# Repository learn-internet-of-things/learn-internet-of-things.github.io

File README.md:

README
======

Jekyll
------

### Windows

Ruby 2.2.5 (x64)

http://rubyinstaller.org/downloads/

Install it for example to `C:\Tools\Ruby22-x64`
Select checkbox "Add Ruby executables to your PATH"

DevKit "for use with Ruby 2.0 and above (x64 - 64bits only)"

http://rubyinstaller.org/downloads/

`C:\Tools\DevKit2`
Add `C:\Tools\DevKit2\bin` to PATH

CMD to `C:\Tools\DevKit2`

```
ruby dk.rb init
ruby dk.rb install
```

Open CMD window.

```
gem install RedCloth -v '4.2.9
gem install bundler
```

Change in CMD to Github pages reposity

```
bundle install
```

Then, the `server.bat` can be used to start the server.

Notes
-----

Markdown

http://kramdown.gettalong.org/quickref.html#footnotes

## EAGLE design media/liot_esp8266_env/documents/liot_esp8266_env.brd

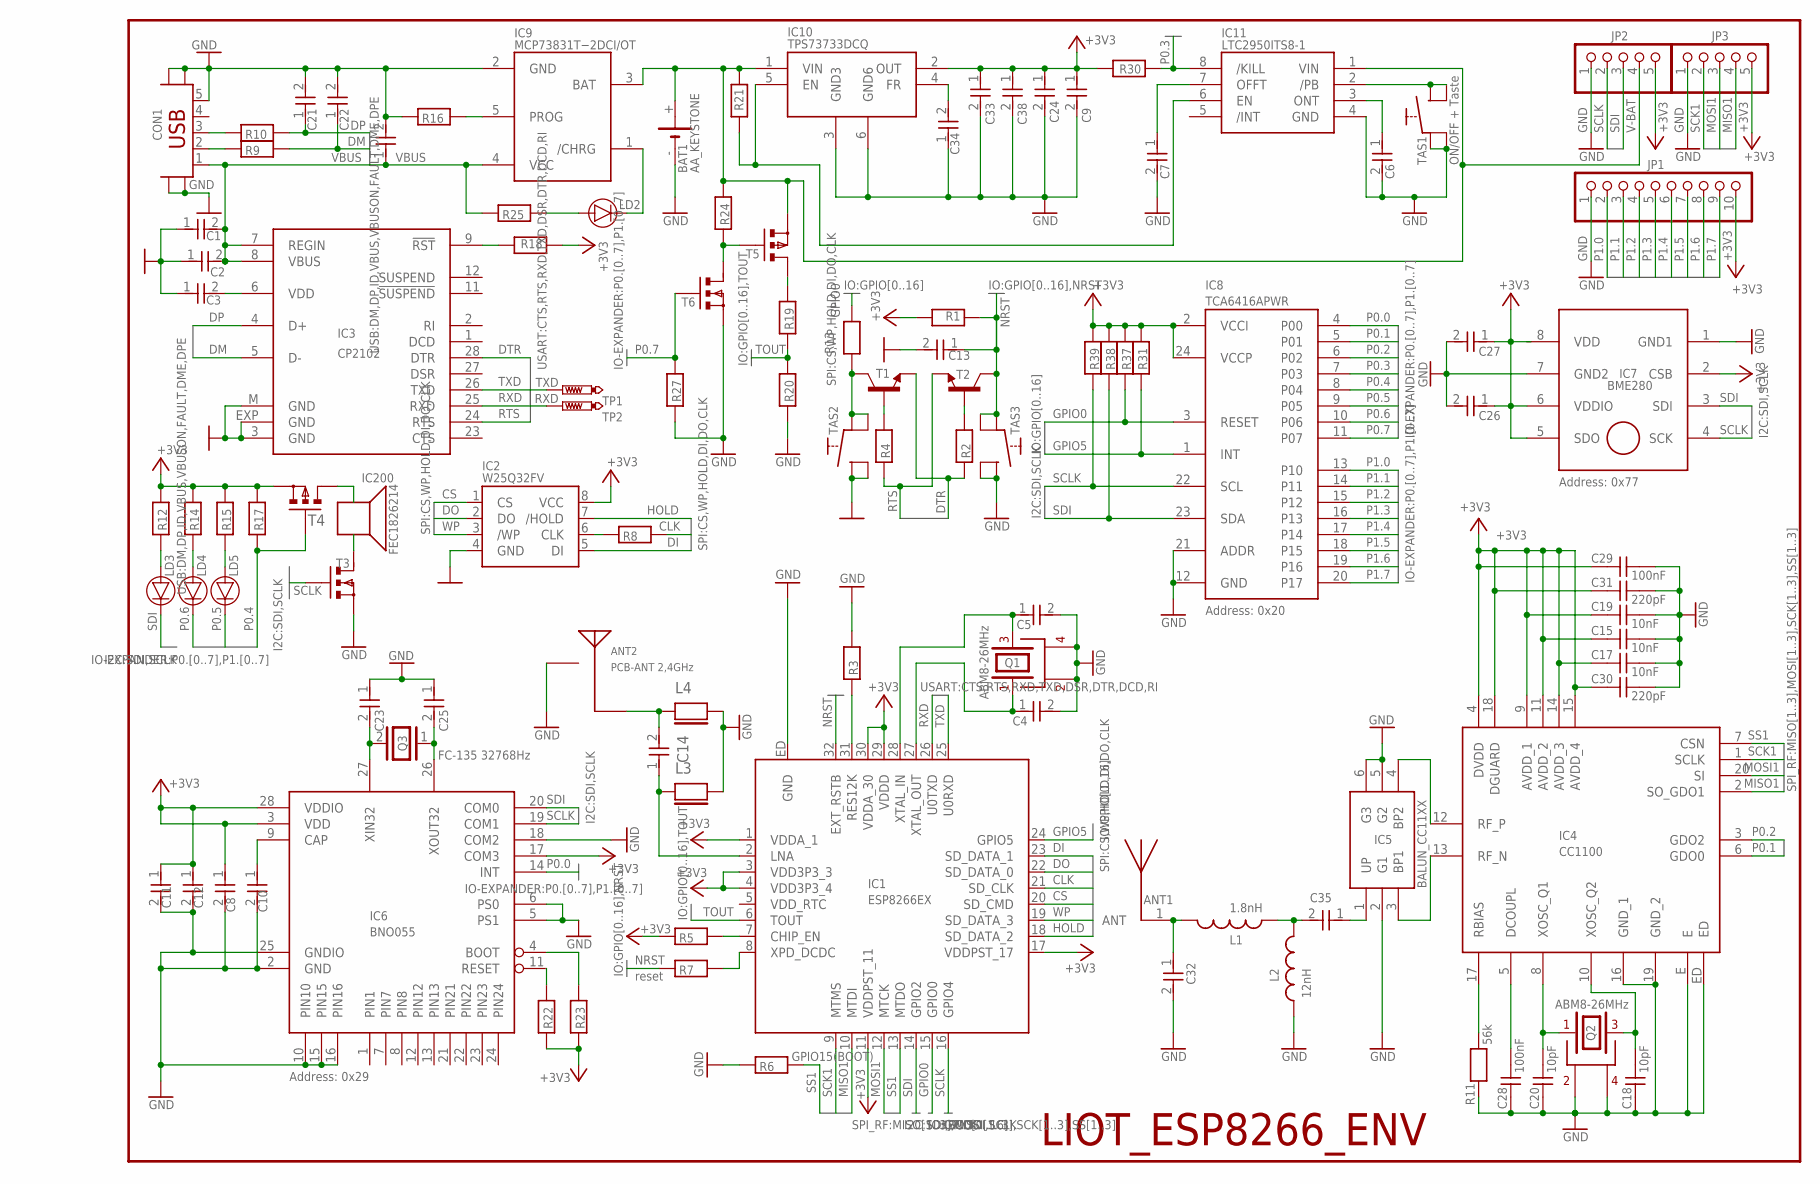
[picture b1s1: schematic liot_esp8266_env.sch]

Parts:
ANT1: ANT_868MHZ
ANT2: PCB-ANT 2,4GHz; 2.4GHZ_PCB
BAT1: AA_KEYSTONE
C1, C2, C3: 1U-16VX7R_0805; C0805
C4, C5, C32: 10P-50VCOG_0603; C0603
C6, C8, C10, C12, C24, C26, C27: 100N-50VX7R_0603; C0603
C7: 330N-16VX7R_0603; C0603
C9: XX-XX-X7R_1210; C1210
C11: 6N8-50VX7R_0603; C0603
C13: 470P-50VX7R_0603; C0603
C14: 5.6pF; C0402
C15, C17, C19: 10nF; C0603
C16, C34: XX-XX-X7R_0805; C0805
C18, C20: 10pF; C0603
C21, C22: 47P-50VCOG_0603; C0603
C23, C25: 22P-50VNP0_0603; C0603
C28, C29: 100nF; C0603
C30, C31: 220pF; C0603
C33, C38: XX-XX-NB-X7R_1210; C1210
C35: 100P-50VCOG_0603; C0603
CON1: MICRO-USB-A/B; MICRO_USB_A/B
IC1: ESP8266EX
IC2: W25Q32FV; SOIC-8_208MIL
IC3: CP2102; MLP28
IC4: CC1100; QLP20E-1+
IC5: BALUN_CC11XX
IC6: BNO055
IC7: BME280
IC8: TCA6416APWR; TSSOP24
IC9: MCP73831T−2DCI/OT; TSOT-23
IC10: TPS73733DCQ; SOT223-6
IC11: LTC2950ITS8-1; TS8
IC200: FEC1826214; BEEPER5X5
JP1: PINHD-1X10; 1X10
JP2, JP3: PINHD-1X5; 1X05
L1: 1.8nH; 0603
L2: 12nH; 0603
L3, L4: NC; L0402
LD2, LD3, LD4, LD5: XXX_0603_H04; LD0603_H04
MA_BS1, MA_BS2: MA_BS_L; MARK_L
MA_LS1, MA_LS2: MA_LS_L; MARK_L
Q1, Q2: ABM8-26MHz; ABM8G
Q3: FC-135 32768Hz; FC-135
R1, R2, R3, R4, R5, R6: 12K-1%_0603; R0603
R7: 0R-1%_0603; R0603
R8: 200R-1%_0603; R0603
R9, R10: 22R-1%_0603; R0603
R11: 56k; R0603
R12, R14, R15, R17: 1K-1%_0603; R0603
R13: 220R-1%_0603; R0603
R16: 2K-1%_0603; R0603
R18, R22, R23, R24, R27, R31, R37, R38, R39: 10K-1%_0603; R0603
R19: 390K-1%_0603; R0603
R20, R21, R30: 100K-1%_0603; R0603
R25: 680R-1%_0603; R0603
T1, T2: BC817-NPN-SOT23-BEC; SOT23-BEC
T3, T6: IRLML2402; SOT23S23
T4, T5: IRLML6402; SOT23S23
TAS1, TAS2, TAS3: 434333045822; TAWU1_S_H18
TP1, TP2: PTR1B1,27; B1,27

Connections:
+3V3: C8.1, C9.1, C11.1, C12.1, C15.1, C17.1, C19.1, C24.1, C26.1, C27.1, C29.1, C30.1, C31.1, C33.1, C38.1, IC1.1 (VDDA_1), IC1.3 (VDD3P3_3), IC1.4 (VDD3P3_4), IC1.11 (VDDPST_11), IC1.17 (VDDPST_17), IC1.29 (VDDD), IC1.30 (VDDA_30), IC2.8 (VCC), IC4.4 (DVDD), IC4.9 (AVDD_1), IC4.11 (AVDD_2), IC4.14 (AVDD_3), IC4.15 (AVDD_4), IC4.18 (DGUARD), IC6.3 (VDD), IC6.17 (COM3), IC6.28 (VDDIO), IC7.2 (CSB), IC7.5 (SDO), IC7.6 (VDDIO), IC7.8 (VDD), IC8.2 (VCCI), IC8.24 (VCCP), IC10.2 (OUT), JP1.10, JP2.5, JP3.5, R1.2, R5.1, R12.2, R14.2, R15.2, R17.2, R18.1, R22.1, R23.1, R30.2, R31.2, R37.2, R38.2, R39.2, T4.2 (S)
/PB: IC11.2 (/PB), TAS1.2 (ON), TAS1.4 (ON1)
CLK: IC1.21 (SD_CLK), R8.2
CS: IC1.20 (SD_CMD), IC2.1 (CS)
DI: IC1.23 (SD_DATA_1), IC2.5 (DI)
DM: C22.1, IC3.5 (D-), R9.1
DME: CON1.2 (D-), R9.2
DO: IC1.22 (SD_DATA_0), IC2.2 (DO)
DP: C21.1, IC3.4 (D+), R10.1
DPE: CON1.3 (D+), R10.2
DTR: IC3.28 (DTR), R2.1, T1.E
GND: ANT2.GND (2), BAT1.-, C1.1, C2.1, C3.1, C4.2, C5.2, C6.2, C7.2, C8.2, C9.2, C10.2, C11.2, C12.2, C13.2, C15.2, C16.2, C17.2, C18.1, C19.2, C20.1, C21.2, C22.2, C23.1, C24.2, C25.1, C26.2, C27.2, C28.1, C29.2, C30.2, C31.2, C32.2, C33.2, C34.1, C38.2, CON1.5 (GND), CON1.S1 (GND), CON1.S2 (GND), CON1.S3 (GND), CON1.S4 (GND), CON1.S5 (GND), CON1.S6 (GND), CON1.S7 (GND), CON1.S8 (GND), CON1.S9 (GND), CON1.S10 (GND), CON1.S11 (GND), CON1.S12 (GND), IC1.ED (GND), IC2.4 (GND), IC3.3 (GND), IC3.EXP (GND), IC3.M (GND), IC4.16 (GND_1), IC4.19 (GND_2), IC4.E, IC4.ED, IC5.2 (G1), IC5.5 (G2), IC5.6 (G3), IC6.2 (GND), IC6.5 (PS1), IC6.6 (PS0), IC6.10 (PIN10), IC6.15 (PIN15), IC6.16 (PIN16), IC6.18 (COM2), IC6.25 (GNDIO), IC7.1 (GND1), IC7.7 (GND2), IC8.12 (GND), IC8.21 (ADDR), IC9.2 (GND), IC10.3 (GND3), IC10.6 (GND6), IC11.4 (GND), JP1.1, JP2.1, JP3.1, L2.1, L3.2, L4.2, Q1.2, Q1.4, Q2.2, Q2.4, R3.2, R6.1, R11.1, R16.1, R20.2, R27.1, T3.2 (S), T6.2 (S), TAS1.1 (COMM), TAS1.3 (COMM1), TAS2.2 (ON), TAS2.4 (ON1), TAS3.2 (ON), TAS3.4 (ON1)
GPIO0: IC1.15 (GPIO0), IC8.3 (RESET), R13.2, R37.1
GPIO5: IC1.24 (GPIO5), IC8.1 (INT), R31.1
HOLD: IC1.18 (SD_DATA_2), IC2.7 (/HOLD)
IC12: IC200.-, T3.3 (D)
MISO1: IC1.10 (MTDI), IC4.2 (SO_GDO1), JP3.4
MOSI1: IC1.12 (MTCK), IC4.20 (SI), JP3.3
unnamed: C4.1, IC1.27 (XTAL_OUT), Q1.1
unnamed: R2.2, T2.B
unnamed: C3.2, IC3.6 (VDD)
unnamed: IC1.7 (CHIP_EN), R5.2
unnamed: R4.2, T1.B
unnamed: IC1.31 (RES12K), R3.1
unnamed: IC1.8 (XPD_DCDC), R7.1
unnamed: IC2.6 (CLK), R8.1
unnamed: C14.1, IC1.2 (LNA), L3.1
unnamed: C18.2, IC4.10 (XOSC_Q2), Q2.3
unnamed: C20.2, IC4.8 (XOSC_Q1), Q2.1
unnamed: IC4.17 (RBIAS), R11.2
unnamed: C28.2, IC4.5 (DCOUPL)
unnamed: C5.1, IC1.28 (XTAL_IN), Q1.3
unnamed: IC9.5 (PROG), R16.2
unnamed: IC9.1 (/CHRG), LD2.2 (K)
unnamed: IC4.13 (RF_N), IC5.3 (BP1)
unnamed: IC4.12 (RF_P), IC5.4 (BP2)
unnamed: ANT1.1, C32.1, L1.2
unnamed: LD2.1 (A), R25.1
unnamed: C35.2, L1.1, L2.2
unnamed: C35.1, IC5.1 (UP)
unnamed: ANT2.ANT (1), C14.2, L4.1
unnamed: IC6.11 (RESET), R22.2
unnamed: IC6.4 (BOOT), R23.2
unnamed: C10.1, IC6.9 (CAP)
unnamed: C23.2, IC6.27 (XIN32), Q3.2
unnamed: IC10.5 (EN), IC11.6 (EN), R21.1
unnamed: C25.2, IC6.26 (XOUT32), Q3.1
unnamed: R13.1, T1.C, TAS2.1 (COMM), TAS2.3 (COMM1)
unnamed: C34.2, IC10.4 (FR)
unnamed: IC200.+, T4.3 (D)
unnamed: LD3.1 (A), R12.1
unnamed: LD4.1 (A), R14.1
unnamed: IC3.9 (!RST), R18.2
unnamed: LD5.1 (A), R15.1
unnamed: R19.2, T5.3 (D)
unnamed: R24.1, T5.1 (G), T6.3 (D)
unnamed: C7.1, IC11.7 (OFFT)
unnamed: C6.1, IC11.3 (ONT)
NRST: C13.1, IC1.32 (EXT_RSTB), R1.1, R7.2, T2.C, TAS3.1 (COMM), TAS3.3 (COMM1)
P0.0: IC6.14 (INT), IC8.4 (P00)
P0.1: IC4.6 (GDO0), IC8.5 (P01)
P0.2: IC4.3 (GDO2), IC8.6 (P02)
P0.3: IC8.7 (P03), IC11.8 (/KILL), R30.1
P0.4: IC8.8 (P04), R17.1, T4.1 (G)
P0.5: IC8.9 (P05), LD5.2 (K)
P0.6: IC8.10 (P06), LD4.2 (K)
P0.7: IC8.11 (P07), R27.2, T6.1 (G)
P1.0: IC8.13 (P10), JP1.2
P1.1: IC8.14 (P11), JP1.3
P1.2: IC8.15 (P12), JP1.4
P1.3: IC8.16 (P13), JP1.5
P1.4: IC8.17 (P14), JP1.6
P1.5: IC8.18 (P15), JP1.7
P1.6: IC8.19 (P16), JP1.8
P1.7: IC8.20 (P17), JP1.9
RTS: IC3.24 (RTS), R4.1, T2.E
RXD: IC1.26 (U0TXD), IC3.25 (RXD), TP2.PP
SCK1: IC1.9 (MTMS), IC4.1 (SCLK), JP3.2
SCLK: IC1.16 (GPIO4), IC6.19 (COM1), IC7.4 (SCK), IC8.22 (SCL), JP2.2, R39.1, T3.1 (G)
SDI: IC1.14 (GPIO2), IC6.20 (COM0), IC7.3 (SDI), IC8.23 (SDA), JP2.3, LD3.2 (K), R38.1
SS1: IC1.13 (MTDO), IC4.7 (CSN), R6.2
TOUT: IC1.6 (TOUT), R19.1, R20.1
TXD: IC1.25 (U0RXD), IC3.26 (TXD), TP1.PP
V-BAT: BAT1.+, IC9.3 (BAT), IC10.1 (VIN), IC11.1 (VIN), JP2.4, R21.2, R24.2, T5.2 (S)
VBUS: C1.2, C2.2, C16.1, CON1.1 (VBUS), IC3.7 (REGIN), IC3.8 (VBUS), IC9.4 (VCC), R25.2
WP: IC1.19 (SD_DATA_3), IC2.3 (/WP)

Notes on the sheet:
ON/OFF + Taste
reset
Address: 0x77
Address: 0x29
Address: 0x20
GPIO15(BOOT)
LIOT_ESP8266_ENV

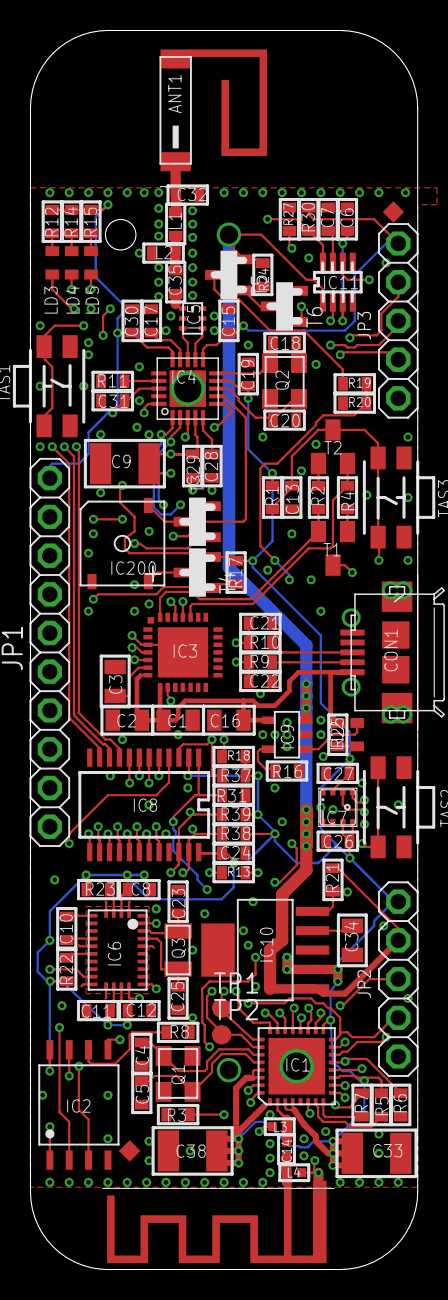
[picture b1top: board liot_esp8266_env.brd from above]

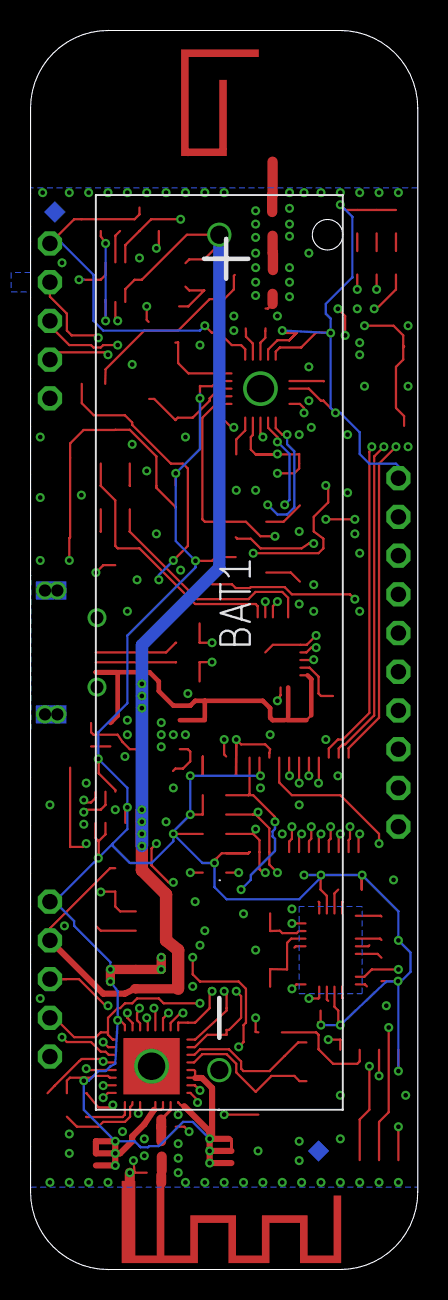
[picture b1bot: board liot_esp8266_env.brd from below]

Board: 4 copper layers, 25.4 x 81.3 mm, 112 parts (3 on the bottom side), 86 nets.

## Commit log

2016-05-26 Sidebar-Nav is working for subpaths now, but not for root
2016-05-26 Add all other jekyll files
2016-05-26 Sidebar-Nav seems to work now also for the root path
2016-05-26 Show only paes in Sidebar-Nav that have a title
2016-05-26 Remove unused order number from page directories.
2016-05-26 Page is looking nice for the first time
2016-05-26 Use https for cnd ressources instead of http.
2016-05-26 Change current canonical url.
2016-06-05 Create CNAME
2016-06-08 Informations about not available hardware i2c
2016-06-08 Remove redcarpet as markdown processor again
2016-06-08 Remove unwanted files from version control
2016-06-08 Complete Pin List for Hardware Design Page
2016-06-09 Finish connection table
2016-06-16 Planning hardware, CPU spec, move table from design to planning.
2016-06-16 Clean up file structure, use permalinks.
2016-07-22 Add board 3D graphic.
2016-07-28 Add all pages and Gemfile.lock
2016-07-29 Use new logo, apply first version of map on liot-esp8266-env graphic.
2016-08-04 Large refactoring removing subdirs, electricity basics.
2016-08-14 Update whole structure, make sidebar-nav static, delete concepts section.
2016-08-14 Add more descriptions to the home graphic.
2016-08-14 Add setup instructions for windows.
2016-08-15 Added missing install instruction
2016-08-17 Add introduction for the home page.
2016-08-19 Add another page to the software category, rename others for order and add images.
2016-08-20 Automatically generated Content Navigation
2016-08-20 Issue #3: fixed (removed) sidenav animation on home page
2016-08-20 Update RF-transceiver and pin assignment in planning table.
2016-08-20 #2 Content-Nav only when h2-Elements are Present
2016-08-20 cleanup
2016-08-20 Tables are now scrollable
2016-08-20 Fix missing index increment.
2016-08-20 Make "Under construction" message more clear.
2016-08-20 Improve intro text.
2016-08-20 Keep proportions of home intro image.
2016-08-20 Integrate hardware basics and interfaces types into hardware sections.
2016-08-20 Improve content and code style.
2016-08-20 Fill IDE page with a basic structure.
2016-08-20 #5 Added FancyBox, enabled it automatically to all Images in the Content Area
2016-08-20 #5 added shadows to content images
2016-08-20 #5 removed the border-shadows back
2016-08-20 #5 workaround for the homepage image -> images with an id dont get the fancybox
2016-08-21 Remove border and shadows from IDE screenshots.
2016-08-23 Add ICs output stages graphics.
2016-08-27 Small fixes.
2016-09-10 #7 better Scollspy, anchors now with their names, headings with anchor-hovers
2016-09-10 Add exemplary smaller image.
2016-09-10 #6 Responsive Naviagtionbar (with Burgerbutton etc), Content Margin on smaller Screens
2016-10-09 #6 New Look for the Left-Nav
2016-10-12 #6 playing with the layout
    new complete different layout
2016-12-04 WIP: Hardware basics and interfaces
2016-12-05 Use fancybox only for resized images and add CSS for image captions
2016-12-05 Add symbols for rcl and supply
2016-12-05 Move output stages graphics to interfaces directory
2016-12-05 Use fancybox for all small-scaled images, allow 'zooming'
2016-12-07 Add hardware design page images
2016-12-07 Add bipolar transistors to electrical components
2016-12-07 Try to fix fancybox problems
2016-12-07 Almost complete basic version of hardware design page
2016-12-07 Add basic content for interfaces page
2017-01-07 Further changes
2017-01-07 Add documentation for sdk setup
2017-01-07 Update references style of basics
2017-01-07 Improve and extend software section
2017-01-08 Start with I2C driver description
2017-01-08 Fix battery runtime duration
2017-01-11 Add references to I/O page
2017-01-11 Add TCA6416A software section.
2017-01-14 Large refactoring.
2017-01-14 Add more board documents.
2017-01-14 Add EAGLE files.
2017-01-14 Add more planning content.
2017-01-15 More planning content.
2017-01-15 Clean up pages
